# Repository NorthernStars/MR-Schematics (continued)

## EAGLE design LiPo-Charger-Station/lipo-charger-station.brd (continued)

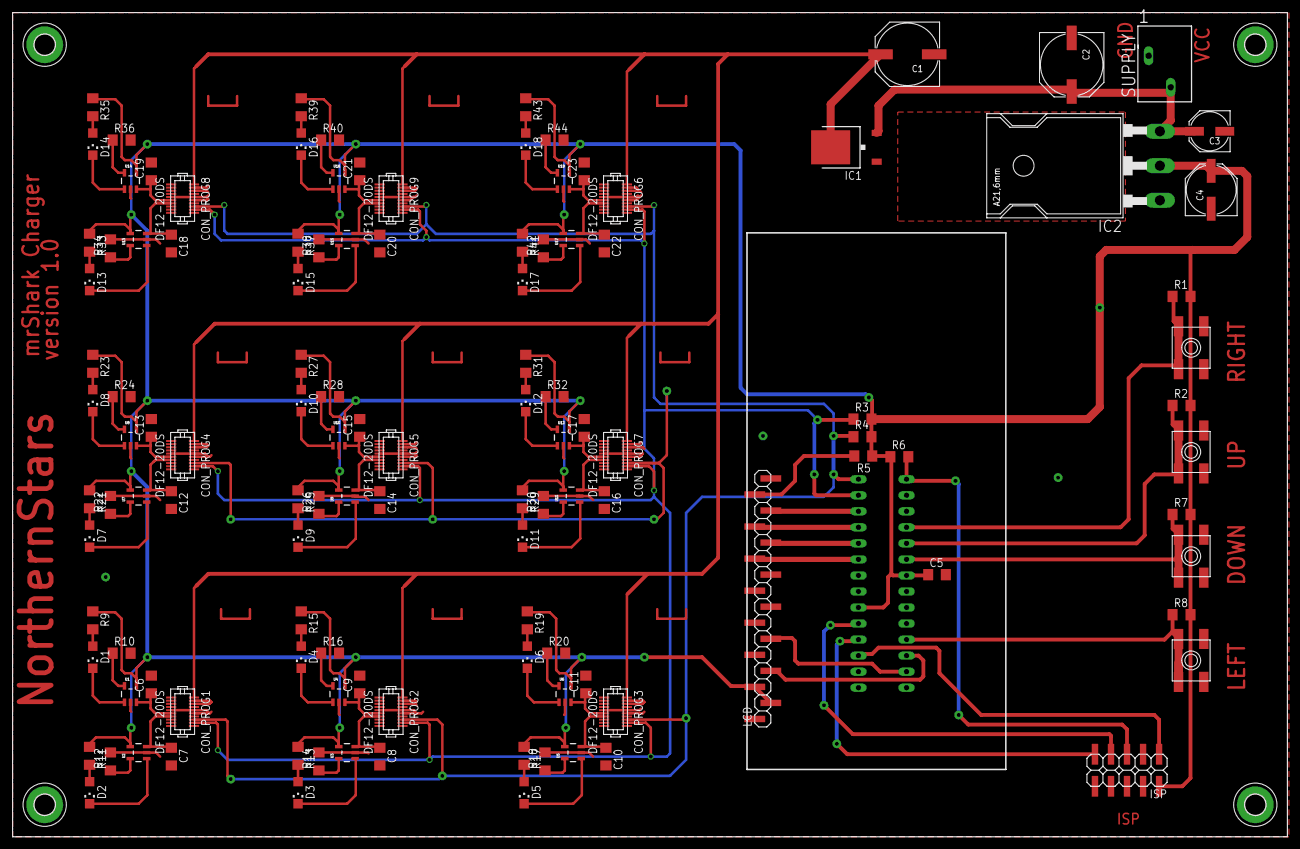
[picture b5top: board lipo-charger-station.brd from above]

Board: 2 copper layers, 201.9 x 130.6 mm, 126 parts (1 on the bottom side), 93 nets.

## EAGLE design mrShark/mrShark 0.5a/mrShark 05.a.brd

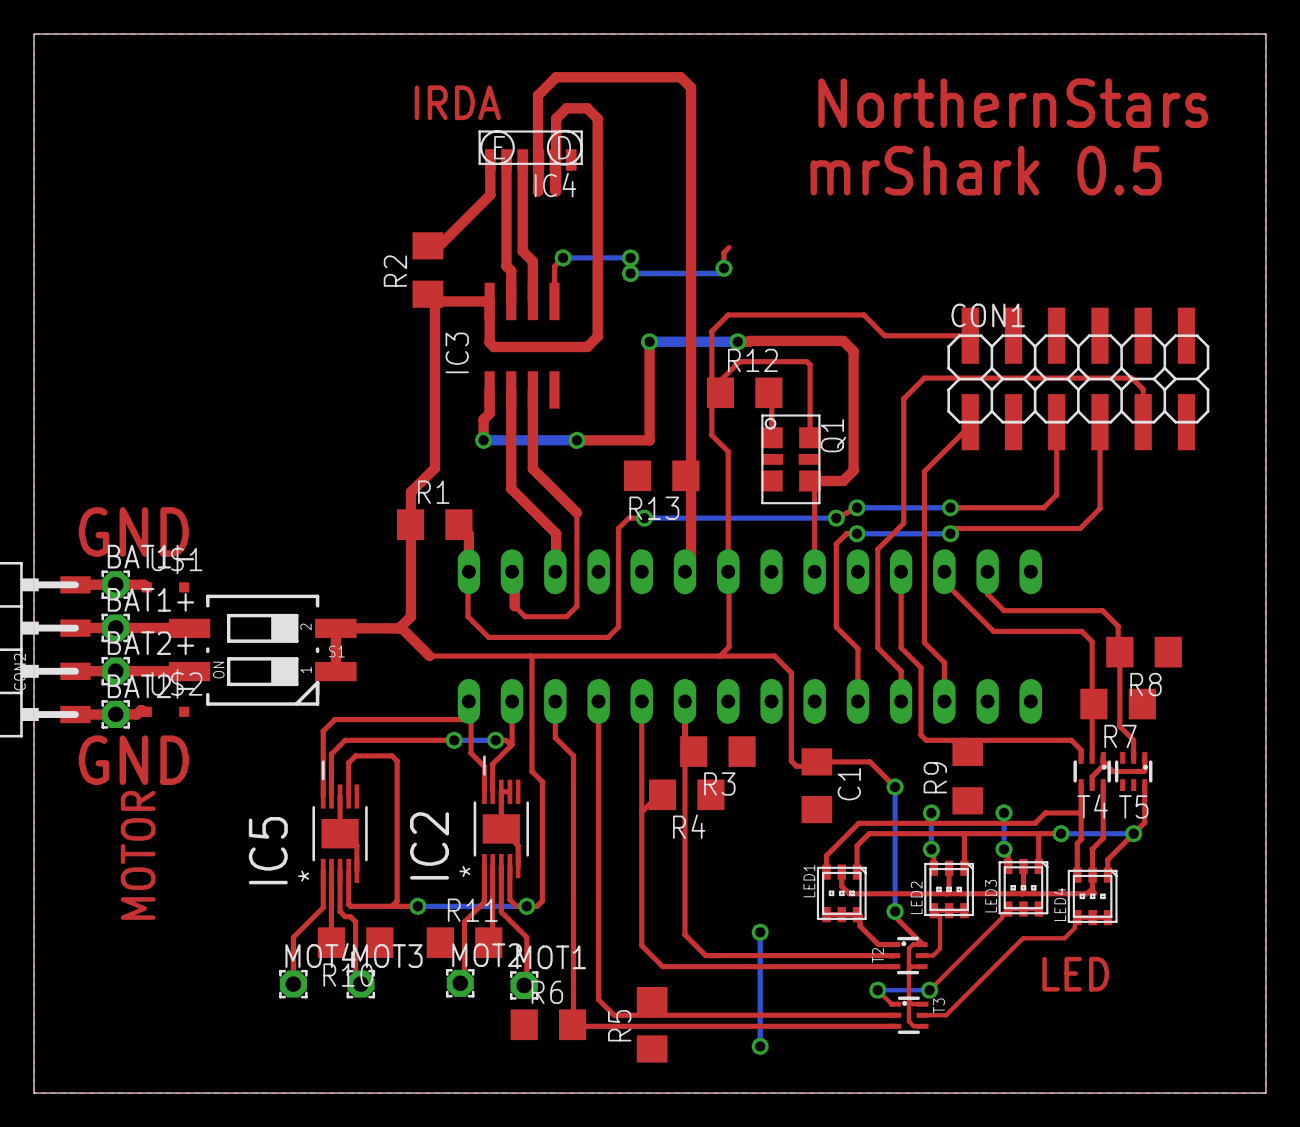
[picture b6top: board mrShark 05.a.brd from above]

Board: 2 copper layers, 72.4 x 62.2 mm, 41 parts (1 on the bottom side), 40 nets.

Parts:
BAT1+, BAT1-, BAT2+, BAT2-: 1,6/0,9
C1: 100n; C1206
CON1: 2X06SMD
CON2: 1X04SMD/90
IC1: MEGA48/88/168-PU; DIL28-3
IC2, IC5: DRV8830DGQRMSOP; SOP65P640X110-15N
IC3: TIR1000PSR; SO-08
IC4: TFBS4711TR1; TFBS4711
LED1, LED2, LED3, LED4: ASMT-YTD2-0BB02; PLCC6
MOT1, MOT2, MOT3, MOT4: 1,6/0,9
Q1: ASFLM1-1.8432MHZ-L-C-T; HC536
R1, R3, R4, R5, R6, R7, R8, R9, R12, R13: 1k; R1206
R2: 27R; R1206
R10, R11: 0.95R; R1206
S1: MCEMR-02-T; CTS-219-02
T2, T3: UMX3NTR; SOT363_INFINEON
T4, T5: UMX3NTR-SOT363; SOT363_INFINEON
U$1, U$2: PMEG2010EAR; SOD323-R

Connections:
BAT1+: BAT1+.1, CON2.3, S1.3
BAT1-: BAT1-.1, CON2.4, U$1.C
BAT2+: BAT2+.1, CON2.2, S1.4
BAT2-: BAT2-.1, CON2.1, U$2.C
CLK: IC1.9, IC3.1, Q1.3
COLOR_B: LED1.1, LED2.1, LED3.1, LED4.1, T5.6
COLOR_G: LED1.2, LED2.2, LED3.2, LED4.2, T4.6
COLOR_R: LED1.3, LED2.3, LED3.3, LED4.3, T4.4
GND: C1.2, CON1.4, CON1.6, CON1.8, CON1.10, IC1.8, IC1.22, IC2.5, IC2.7, IC2.8, IC2.11, IC3.4, IC3.5, IC4.6, IC5.5, IC5.8, IC5.11, Q1.2, R3.1, R4.1, R5.1, R6.1, R7.1, R8.1, R9.1, R10.1, R11.1, R13.2, T4.1, T4.5, T5.1, U$1.A, U$2.A
IRDA: IC4.1, R2.2
IR_SD: IC1.6, IC4.4, R13.1
LED1: IC1.23, R3.2, T2.2
LED1+: LED1.4, LED1.5, LED1.6, T2.1
LED2: IC1.24, R4.2, T2.3
LED2+: LED2.4, LED2.5, LED2.6, T2.5
LED3: IC1.25, R5.2, T3.2
LED3+: LED3.4, LED3.5, LED3.6, T3.1
LED4: IC1.26, R6.2, T3.3
LED4+: LED4.4, LED4.5, LED4.6, T3.5
LED_B: IC1.13, R8.2, T5.2
LED_G: IC1.12, R7.2, T4.2
LED_R: IC1.11, R9.2, T4.3
MISO: CON1.9, IC1.18
MOSI: CON1.1, IC1.17
unnamed: IC5.3, MOT3.1
unnamed: IC5.1, MOT4.1
unnamed: Q1.1, R12.2
unnamed: IC5.2, R10.2
unnamed: IC2.2, R11.2
unnamed: IC2.3, MOT1.1
unnamed: IC2.1, MOT2.1
RESET: CON1.5, IC1.1, R1.2
RXD: IC1.2, IC3.3
RXIR: IC3.6, IC4.3
SCK: CON1.7, IC1.19
SCL: IC1.28, IC2.10, IC5.10
SDA: IC1.27, IC2.9, IC5.9
TXD: IC1.3, IC3.2
TXIR: IC3.7, IC4.2
VCC: C1.1, CON1.2, IC1.7, IC2.4, IC3.8, IC4.5, IC5.4, IC5.7, Q1.4, R1.1, R2.1, R12.1, S1.1, S1.2, T2.4, T2.6, T3.4, T3.6
